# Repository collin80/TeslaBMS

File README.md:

Arduino compatible project to interface with the BMS slave 
board on Tesla Model S modules.

The modules are daisy-chained together with a TTL interface.
The interface uses a Molex 15-97-5101 connector and runs at
612500 baud. This can be a difficult baud rate to match with
arduino compatible processors. The Arduino Due and Teensy
3.5/3.6 boards are confirmed to be able to generate a suitably
close baud rate. The factory wiring to each module is comprised
of two sets of 5 differently colored wires:

* Red = 5V input to the module
* Green = Gnd for power and signal
* Gray = Fault output
* Yellow = UART Wire
* Blue = UART Wire

The fault output is active low. Use your own pull up to the fault line and if the line is pulled low then a fault has occurred.

Here is a PDF that explains how the wiring between modules and the master board is supposed to be:
https://cdn.hackaday.io/files/10098432032832/wiring.pdf

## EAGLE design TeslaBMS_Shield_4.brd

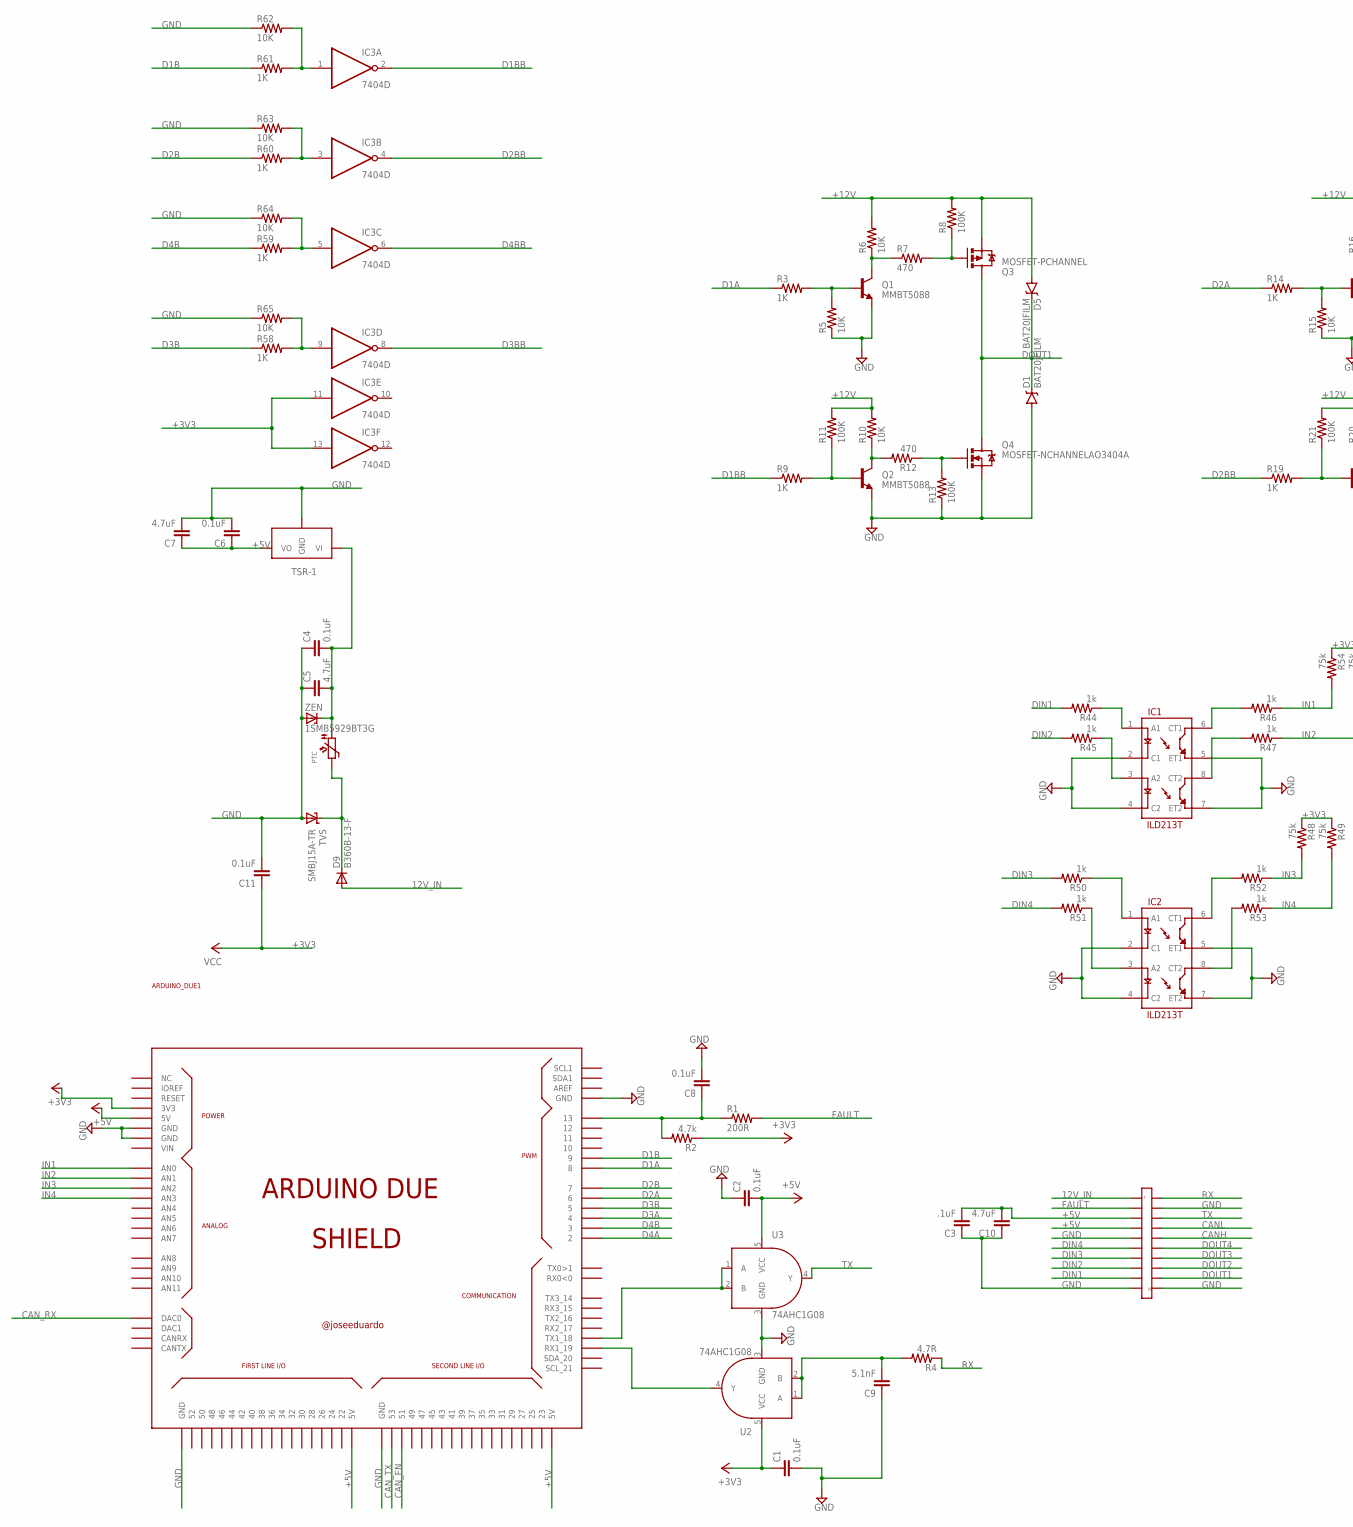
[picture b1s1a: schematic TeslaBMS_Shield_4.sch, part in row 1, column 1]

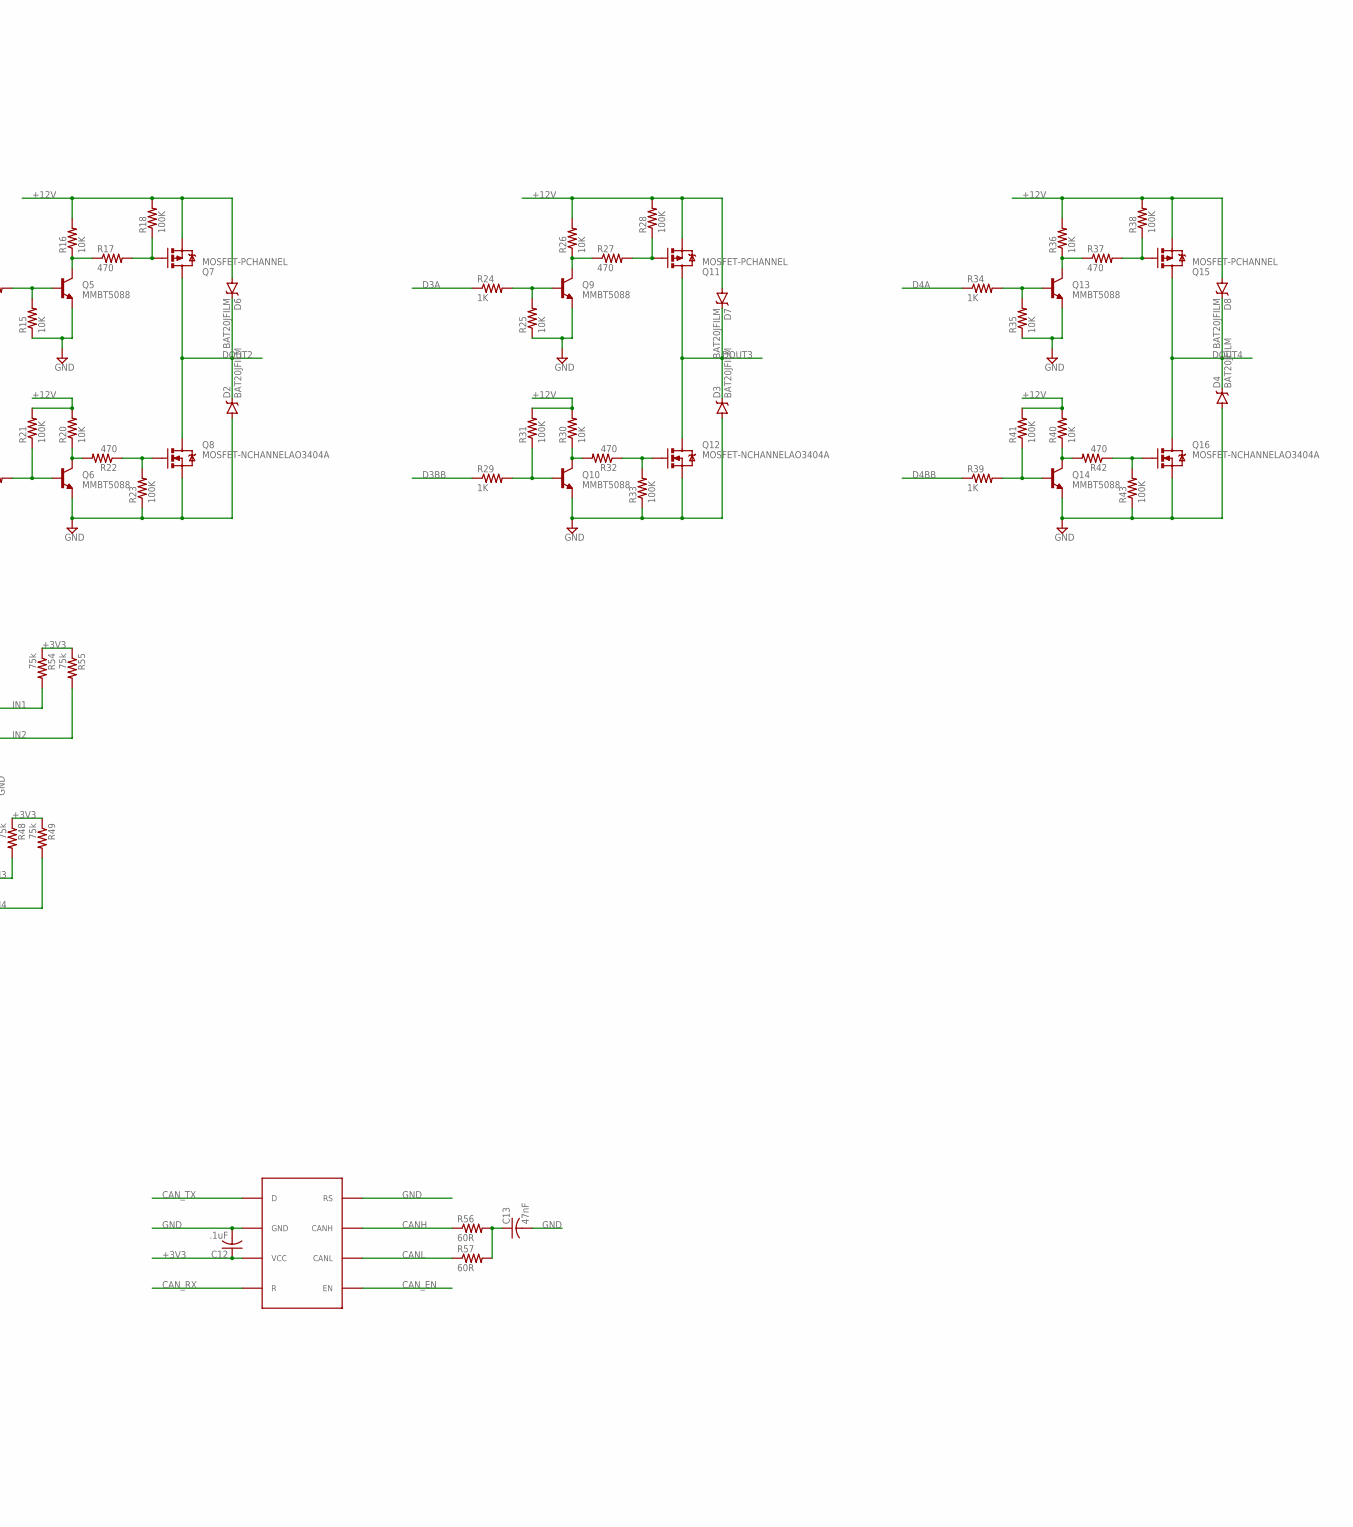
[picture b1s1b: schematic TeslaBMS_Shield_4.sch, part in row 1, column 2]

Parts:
ARDUINO_DUE1: ARDUINO_DUE_SHIELD
C1, C2, C8: 0.1uF; 0603-CAP
C3: .1uF; 0603-CAP
C4, C6, C11: 0.1uF; 0805
C5, C7: 4.7uF; 0805
C9: 5.1nF; 0603-CAP
C10: 4.7uF; 0603-CAP
C12: .1uF; C0603
C13: 47nF; C0805
D1, D2, D3, D4, D5, D6, D7, D8: BAT20JFILM; SOD-323
D9: B360B-13-F; SMB
IC1, IC2: ILD213T; SO08
IC3: 7404D; SO14
PTC: PTC1812
Q1, Q2, Q5, Q6, Q9, Q10, Q13, Q14: MMBT5088; SOT23-3
Q3, Q7, Q11, Q15: MOSFET-PCHANNEL; SOT23-3
Q4, Q8, Q12, Q16: MOSFET-NCHANNELAO3404A; SOT23-3
R1: 200R; 0603-RES
R2: 4.7k; 0603-RES
R3, R9, R14, R19, R24, R29, R34, R39, R58, R59, R60, R61: 1K; 0402-RES
R4: 4.7R; 0603-RES
R5, R6, R10, R15, R16, R20, R25, R26, R30, R35, R36, R40, R62, R63, R64, R65: 10K; 0402-RES
R7, R12, R17, R22, R27, R32, R37, R42: 470; 0402-RES
R8, R11, R13, R18, R21, R23, R28, R31, R33, R38, R41, R43: 100K; 0402-RES
R44, R45, R46, R47, R50, R51, R52, R53: 1k; 0603-RES
R48, R49, R54, R55: 75k; 0603-RES
R56, R57: 60R; M0805
TVS: SMBJ15A-TR; SMBJ
U1: SN65HVD234; SOIC8
U2, U3: 74AHC1G08; SOT353
U9: TSR-1
U$2: VAL-U-LOK-20PIN; VALULOK-20
ZEN: 1SMB5929BT3G; SMB

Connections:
12V_IN: D9.A, U$2.P$1
+3V3: ARDUINO_DUE1.3V3, C1.1, C11.1, C12.1, IC3.11 (I), IC3.13 (I), IC3.14 (VCC), R2.1, R48.1, R49.1, R54.1, R55.1, U1.PIN3 (VCC), U2.5 (VCC)
+5V: ARDUINO_DUE1.5V0 (5V), ARDUINO_DUE1.5V0_1 (5V), ARDUINO_DUE1.5V0_2 (5V), C2.2, C3.2, C6.1, C7.1, C10.2, U3.5 (VCC), U9.P$3 (VO), U$2.P$3, U$2.P$4
+12V: C4.2, C5.2, D5.A, D6.A, D7.A, D8.A, PTC.P$1 (1), Q3.2 (S), Q7.2 (S), Q11.2 (S), Q15.2 (S), R6.2, R8.2, R10.2, R11.2, R16.2, R18.2, R20.2, R21.2, R26.2, R28.2, R30.2, R31.2, R36.2, R38.2, R40.2, R41.2, U9.P$1 (VI), ZEN.C
CANH: R56.1, U1.PIN7 (CANH), U$2.P$15
CANL: R57.1, U1.PIN6 (CANL), U$2.P$14
CAN_EN: ARDUINO_DUE1.51, U1.PIN5 (EN)
CAN_RX: ARDUINO_DUE1.DAC0, U1.PIN4 (R)
CAN_TX: ARDUINO_DUE1.53, U1.PIN1 (D)
D1A: ARDUINO_DUE1.8, R3.1
D1B: ARDUINO_DUE1.9, R61.1
D1BB: IC3.2 (O), R9.1
D2A: ARDUINO_DUE1.6, R14.1
D2B: ARDUINO_DUE1.7, R60.1
D2BB: IC3.4 (O), R19.1
D3A: ARDUINO_DUE1.4, R24.1
D3B: ARDUINO_DUE1.5, R58.1
D3BB: IC3.8 (O), R29.1
D4A: ARDUINO_DUE1.2, R34.1
D4B: ARDUINO_DUE1.3, R59.1
D4BB: IC3.6 (O), R39.1
DIN1: R44.2, U$2.P$9
DIN2: R45.2, U$2.P$8
DIN3: R50.2, U$2.P$7
DIN4: R51.2, U$2.P$6
DOUT1: D1.C, D5.C, Q3.3 (D), Q4.3 (D), U$2.P$19
DOUT2: D2.C, D6.C, Q7.3 (D), Q8.3 (D), U$2.P$18
DOUT3: D3.C, D7.C, Q11.3 (D), Q12.3 (D), U$2.P$17
DOUT4: D4.C, D8.C, Q15.3 (D), Q16.3 (D), U$2.P$16
FAULT: R1.2, U$2.P$2
GND: ARDUINO_DUE1.GND, ARDUINO_DUE1.GND_1 (GND), ARDUINO_DUE1.GND_2 (GND), ARDUINO_DUE1.GND_3 (GND), ARDUINO_DUE1.GND_4 (GND), C1.2, C2.1, C3.1, C4.1, C5.1, C6.2, C7.2, C8.2, C9.1, C10.1, C11.2, C12.2, C13.2, D1.A, D2.A, D3.A, D4.A, IC1.2 (C1), IC1.4 (C2), IC1.5 (ET1), IC1.7 (ET2), IC2.2 (C1), IC2.4 (C2), IC2.5 (ET1), IC2.7 (ET2), IC3.7 (GND), Q1.2 (E), Q2.2 (E), Q4.2 (S), Q5.2 (E), Q6.2 (E), Q8.2 (S), Q9.2 (E), Q10.2 (E), Q12.2 (S), Q13.2 (E), Q14.2 (E), Q16.2 (S), R5.1, R13.1, R15.1, R23.1, R25.1, R33.1, R35.1, R43.1, R62.1, R63.1, R64.1, R65.1, TVS.A, U1.PIN2 (GND), U1.PIN8 (RS), U2.3 (GND), U3.3 (GND), U9.P$2 (GND), U$2.P$5, U$2.P$10, U$2.P$12, U$2.P$20, ZEN.A
IN1: ARDUINO_DUE1.A0 (AN0), R46.1, R54.2
IN2: ARDUINO_DUE1.A1 (AN1), R47.1, R55.2
IN3: ARDUINO_DUE1.A2 (AN2), R48.2, R52.1
IN4: ARDUINO_DUE1.A3 (AN3), R49.2, R53.1
unnamed: D9.C, PTC.P$2 (2), TVS.C
unnamed: ARDUINO_DUE1.19 (RX1_19), U2.4 (Y)
unnamed: ARDUINO_DUE1.18 (TX1_18), U3.1 (A), U3.2 (B)
unnamed: Q1.1 (B), R3.2, R5.2
unnamed: Q3.1 (G), R7.2, R8.1
unnamed: IC1.3 (A2), R45.1
unnamed: ARDUINO_DUE1.13, C8.1, R1.1, R2.2
unnamed: Q1.3 (C), R6.1, R7.1
unnamed: C9.2, R4.2, U2.1 (A), U2.2 (B)
unnamed: Q5.1 (B), R14.2, R15.2
unnamed: Q2.1 (B), R9.2, R11.1
unnamed: Q4.1 (G), R12.1, R13.2
unnamed: Q2.3 (C), R10.1, R12.2
unnamed: Q5.3 (C), R16.1, R17.1
unnamed: Q7.1 (G), R17.2, R18.1
unnamed: Q6.1 (B), R19.2, R21.1
unnamed: Q8.1 (G), R22.1, R23.2
unnamed: Q6.3 (C), R20.1, R22.2
unnamed: Q9.1 (B), R24.2, R25.2
unnamed: Q9.3 (C), R26.1, R27.1
unnamed: Q11.1 (G), R27.2, R28.1
unnamed: Q10.1 (B), R29.2, R31.1
unnamed: Q12.1 (G), R32.1, R33.2
unnamed: Q10.3 (C), R30.1, R32.2
unnamed: Q13.1 (B), R34.2, R35.2
unnamed: Q13.3 (C), R36.1, R37.1
unnamed: Q15.1 (G), R37.2, R38.1
unnamed: Q14.1 (B), R39.2, R41.1
unnamed: Q16.1 (G), R42.1, R43.2
unnamed: Q14.3 (C), R40.1, R42.2
unnamed: IC1.1 (A1), R44.1
unnamed: IC2.6 (CT1), R52.2
unnamed: C13.1, R56.2, R57.2
unnamed: IC3.9 (I), R58.2, R65.2
unnamed: IC3.5 (I), R59.2, R64.2
unnamed: IC2.8 (CT2), R53.2
unnamed: IC1.6 (CT1), R46.2
unnamed: IC1.8 (CT2), R47.2
unnamed: IC3.3 (I), R60.2, R63.2
unnamed: IC3.1 (I), R61.2, R62.2
unnamed: IC2.1 (A1), R50.1
unnamed: IC2.3 (A2), R51.1
RX: R4.1, U$2.P$11
TX: U3.4 (Y), U$2.P$13

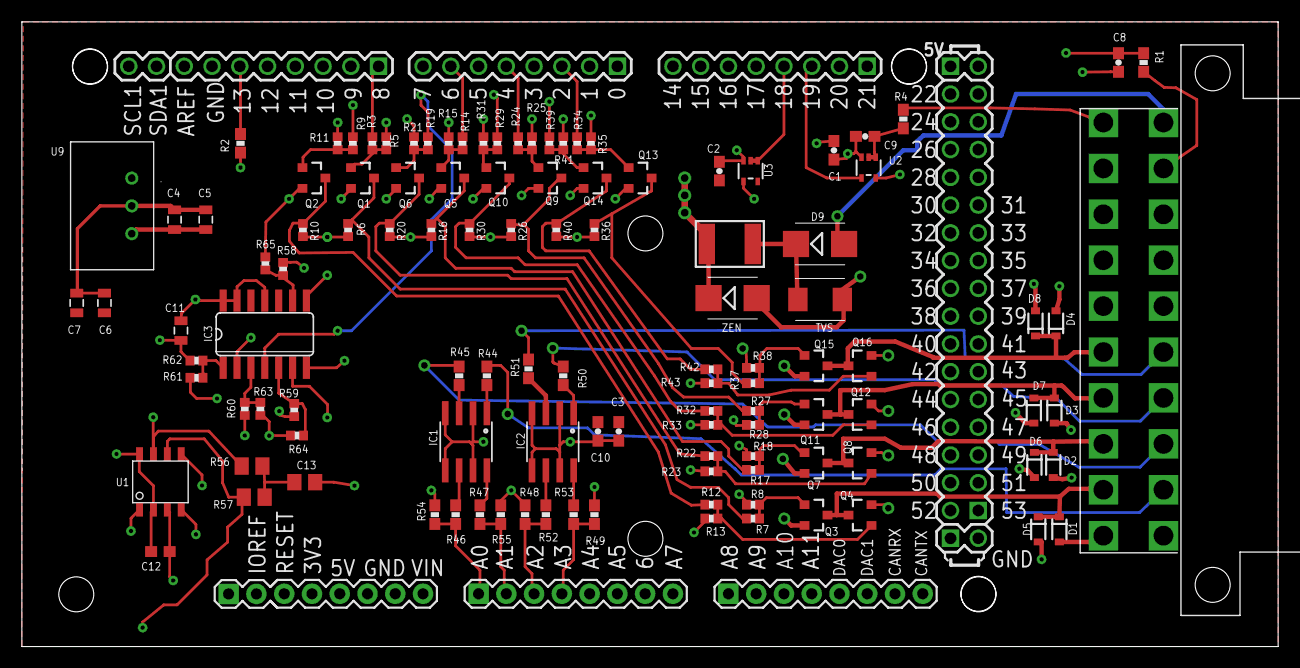
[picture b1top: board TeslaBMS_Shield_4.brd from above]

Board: 4 copper layers, 114.9 x 57.1 mm, 115 parts (0 on the bottom side), 79 nets.

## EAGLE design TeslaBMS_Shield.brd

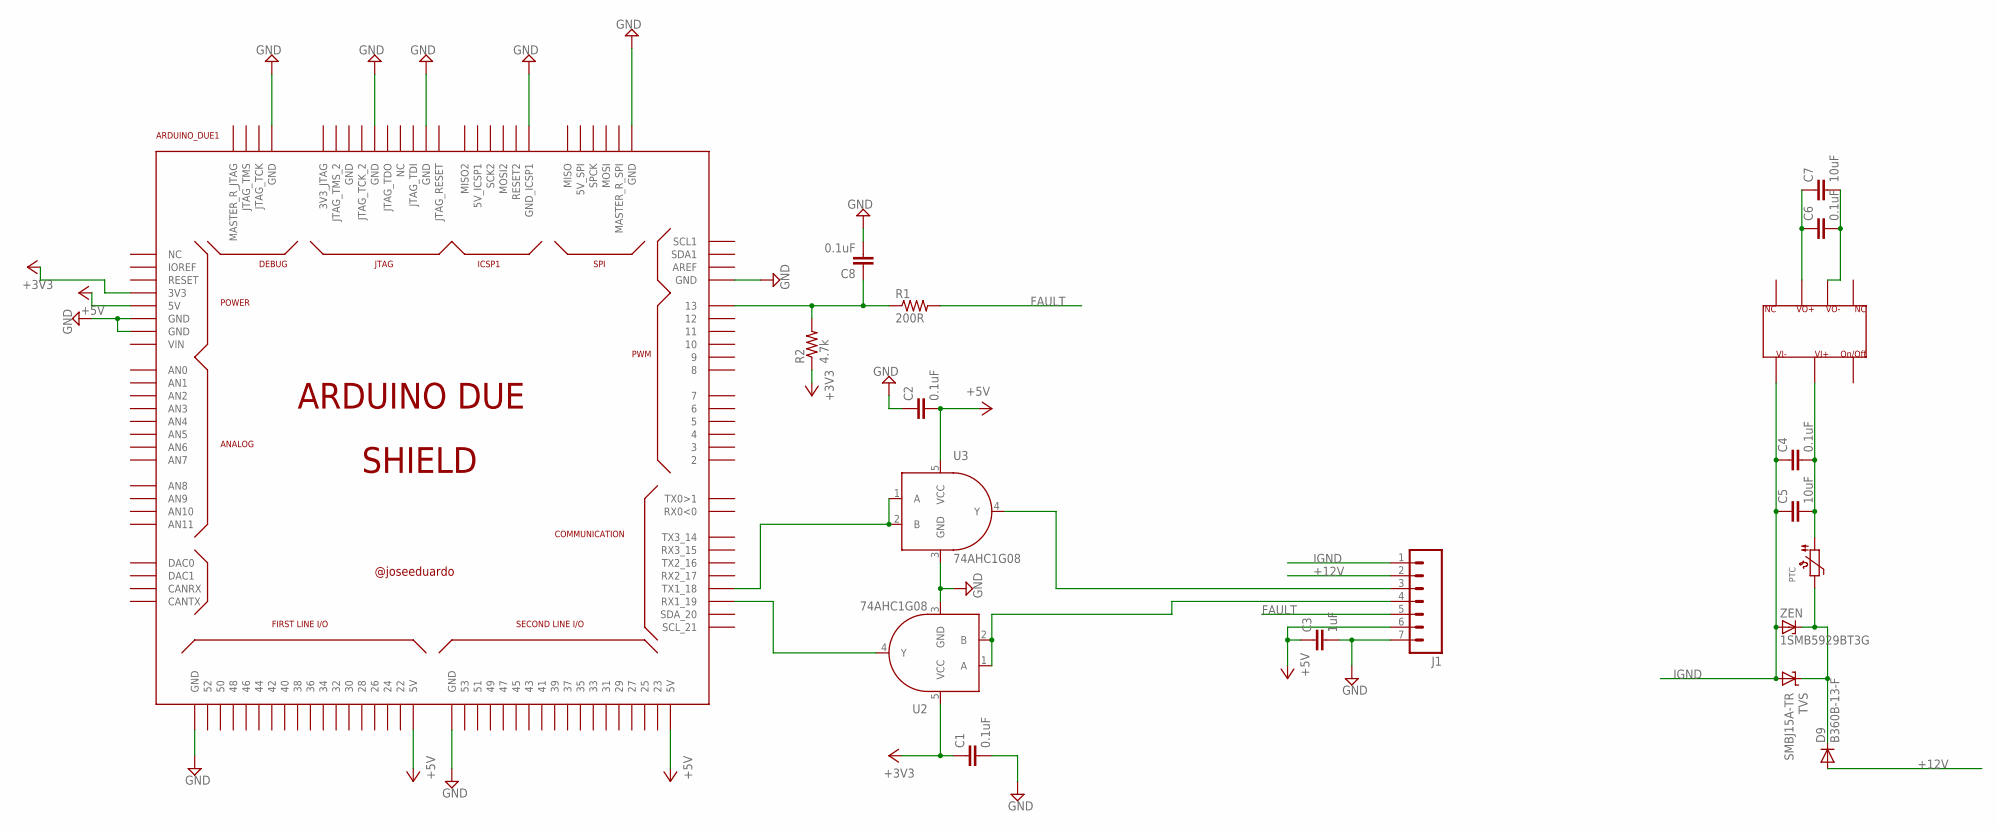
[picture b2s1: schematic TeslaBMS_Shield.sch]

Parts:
ARDUINO_DUE1: ARDUINO_DUE_SHIELD
C1, C2, C8: 0.1uF; 0603-CAP
C3: 1uF; 0603-CAP
C4, C6: 0.1uF; 0805
C5, C7: 10uF; 0805
D9: B360B-13-F; SMB
J1: M07LONGPADS; 1X07_LONGPADS
PTC: PTC1812
R1: 200R; 0603-RES
R2: 4.7k; 0603-RES
TVS: SMBJ15A-TR; SMBJ
U1: CINCON5V
U2, U3: 74AHC1G08; SOT353
ZEN: 1SMB5929BT3G; SMB

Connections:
+3V3: ARDUINO_DUE1.3V3, C1.1, R2.1, U2.5 (VCC)
+5V: ARDUINO_DUE1.5V0 (5V), ARDUINO_DUE1.5V0_1 (5V), ARDUINO_DUE1.5V0_2 (5V), C2.2, C3.1, C6.1, C7.1, J1.6, U1.P$5, U3.5 (VCC)
+12V: D9.A, J1.2
FAULT: J1.5, R1.2
GND: ARDUINO_DUE1.GND, ARDUINO_DUE1.GND_1 (GND), ARDUINO_DUE1.GND_2 (GND), ARDUINO_DUE1.GND_3 (GND), ARDUINO_DUE1.GND_4 (GND), ARDUINO_DUE1.GND_5 (GND), ARDUINO_DUE1.GND_7 (GND), ARDUINO_DUE1.GND_9 (GND), ARDUINO_DUE1.GND_10 (GND), ARDUINO_DUE1.GND_ICSP1, C1.2, C2.1, C3.2, C6.2, C7.2, C8.2, J1.7, U1.P$6, U2.3 (GND), U3.3 (GND)
IGND: C4.1, C5.1, J1.1, TVS.A, U1.P$1, ZEN.A
unnamed: D9.C, PTC.P$2 (2), TVS.C, ZEN.C
unnamed: ARDUINO_DUE1.19 (RX1_19), U2.4 (Y)
unnamed: ARDUINO_DUE1.18 (TX1_18), U3.1 (A), U3.2 (B)
unnamed: J1.3, U3.4 (Y)
unnamed: J1.4, U2.1 (A), U2.2 (B)
unnamed: C4.2, C5.2, PTC.P$1 (1), U1.P$2
unnamed: ARDUINO_DUE1.13, C8.1, R1.1, R2.2

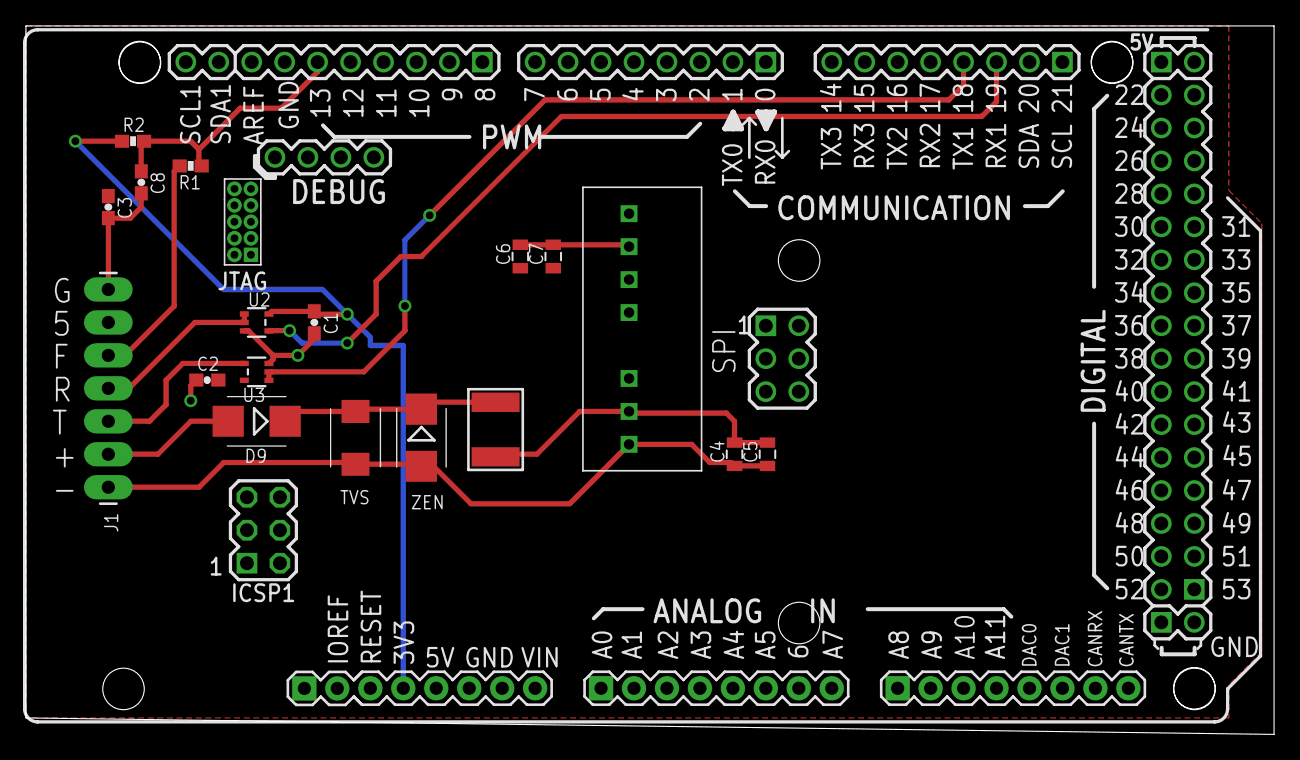
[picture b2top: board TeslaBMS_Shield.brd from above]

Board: 2 copper layers, 96.2 x 54.6 mm, 19 parts (0 on the bottom side), 13 nets.

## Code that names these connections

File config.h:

#pragma once

#include <Arduino.h>

//Set to the proper port for your USB connection - SerialUSB on Due (Native) or Serial for Due (Programming) or Teensy
#define SERIALCONSOLE   SerialUSB

//Define this to be the serial port the Tesla BMS modules are connected to.
//On the Due you need to use a USART port (Serial1, Serial2, Serial3) and update the call to serialSpecialInit if not Serial1
#define SERIAL  Serial1

#define REG_DEV_STATUS      0
#define REG_GPAI            1
#define REG_VCELL1          3
#define REG_VCELL2          5
#define REG_VCELL3          7
#define REG_VCELL4          9
#define REG_VCELL5          0xB
#define REG_VCELL6          0xD
#define REG_TEMPERATURE1    0xF
#define REG_TEMPERATURE2    0x11
#define REG_ALERT_STATUS    0x20
#define REG_FAULT_STATUS    0x21
#define REG_COV_FAULT       0x22
#define REG_CUV_FAULT       0x23
#define REG_ADC_CTRL        0x30
#define REG_IO_CTRL         0x31
#define REG_BAL_CTRL        0x32
#define REG_BAL_TIME        0x33
#define REG_ADC_CONV        0x34
#define REG_ADDR_CTRL       0x3B

#define MAX_MODULE_ADDR     0x3E

#define EEPROM_VERSION      0x10    //update any time EEPROM struct below is changed.
#define EEPROM_PAGE         0

#define DIN1                55
#define DIN2                54
#define DIN3                57
#define DIN4                56
#define DOUT4_H             2
#define DOUT4_L             3
#define DOUT3_H             4
#define DOUT3_L             5
#define DOUT2_H             6
#define DOUT2_L             7
#define DOUT1_H             8
#define DOUT1_L             9

typedef struct {
    uint8_t version;
    uint8_t checksum;
    uint32_t canSpeed;
    uint8_t batteryID;  //which battery ID should this board associate as on the CAN bus
    uint8_t logLevel;
    float OverVSetpoint;
    float UnderVSetpoint;
    float OverTSetpoint;
    float UnderTSetpoint;
    float balanceVoltage;
    float balanceHyst;
} EEPROMSettings;

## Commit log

2017-02-17 Additional initial implementation of functionality
2017-02-17 It compiles now (whoops) and was tested to work to scan for modules.
2017-02-19 Fix a few bugs, add some notes, add more serial console output.
2017-02-19 Fix serial init on Due
2017-02-19 A bunch of fixes from tomdebree. Adds better logging functionality as well. Also, source is now easier to adapt to other processors.
2017-02-19 Selectively compile Due specific code only when actually compiling for Due.
2017-02-19 Add readme file. Very preliminary!
2017-02-19 Ability to renumber all boards from tomdebree. Fixed up weirdness with array accesses - everything should be consistent now.
2017-02-19 Add preliminary balancing support (via tomdebree), fix up more console feedback to be generic.
2017-02-19 The max module address is 62 not 63 so code has been corrected. Now max address is a compile time constant.
2017-02-19 It's possible to broadcast the reset command so now the renumber function uses a broadcast reset which is a lot simpler.
2017-02-20 Small commenting tweaks, log formatting
2017-02-21 Update TeslaBMS.ino
    Added the Clear faults, read faults, read setpoints, sleep and wake commands
2017-02-21 Fix regression added a few commits back that broke register writes to BMS chip. Change getReply to take a max length so that buffer overflows do not happen.
2017-02-22 Preliminary version of a shield to go over an EVTVDue
2017-02-24 Massive code overhaul to make things object oriented and better organized. Not complete yet but compiles and things were getting rather long for a single commit.
2017-02-28 Some refactoring, additional implementation to make code usable again.
2017-02-28 Fix off by one error
2017-02-28 Convert temperatures to ratio, show temperatures in debugging info
2017-02-28 Add a lot more configuration related code. Add theoretically necessary code to voltage/temperature retrieval.
2017-03-09 Added canbus output and setup of input
2017-03-09 Add a whole lot more data tracking in order to better support new CAN protocol.
2017-03-12 Small bug fixes
2017-03-13 MANY bug fixes. Recent past versions weren't operable.
2017-03-13 Added a prettier status screen, some code fixes
2017-03-13 Add averages to pack status, reformat status messages a bit.
2017-03-14 Added the rest of the config items to serial console and implemented saving those settings to EEPROM
2017-03-14 More bug fixing to make things more reliable. Some tweaking of visuals. Addition of fault status output
2017-03-14 Fix fault clearing to actually work, add retrieval of faults and alerts.
2017-03-14 Remove old notes, add new notes
2017-03-14 Reformatting of some source code, reworked the code for renumbering modules and finding modules to work more robustly.
2017-03-14 Make fault clearing more robust
2017-03-14 Tweaked temperature calculations to be seemingly more accurate. Added fault and alert listing on pack status screen
2017-03-14 Switched from third order approximation to steinhart-hart equation for temperatures. So far, it seems better.
2017-03-15 Added a detailed pack screen with all cell voltages and module temperatures
2017-05-01 Added system IO code for new boards
2017-06-04 Source reformatting, fixed cell balancing, implemented hysteresis for balancing
2017-06-05 Inputs are out of order on board so here's a header change to correct that in software.
2017-12-08 Add more versions of board
2018-02-18 Update readme file
2018-03-23 Track good vs bad packets and allow for baud rate changing more easily.

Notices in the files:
parts and their libraries:
SparkFun-DigitalIC: Licensing: Creative Commons ShareAlike 4.0 International - https://creativecommons.org/licenses/by-sa/4.0
microbuilder: This work is placed in the public domain, and may be freely used for commercial and non-commercial work with the following conditions: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
